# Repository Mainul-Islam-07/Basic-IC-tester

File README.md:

# Basic-IC-tester

TinkerCad Simulation Links

https://www.tinkercad.com/things/fH9ZXDevmyo-ic-tester

https://www.tinkercad.com/things/dbMPnGqOklm-ic-tester

Features: 

1) Checks all ports of a basic logic ic (AND , OR, NOT, NOR, NAND, XOR gates) and detects the specific ic and show whether all the ports are okay or whether the ic is damaged. There are 3 slots for placing ICs to check as all basic ic pin configurations are not the same.

2) The output ( either the ic name , or if damaged displays damaged) is shown in a LCD displau

3) The output is then transmitted as msg to a phone number via Sim800L module

** Both hardware and software simulations were done.

The repository contains the pcb files as well as the arduino code required.

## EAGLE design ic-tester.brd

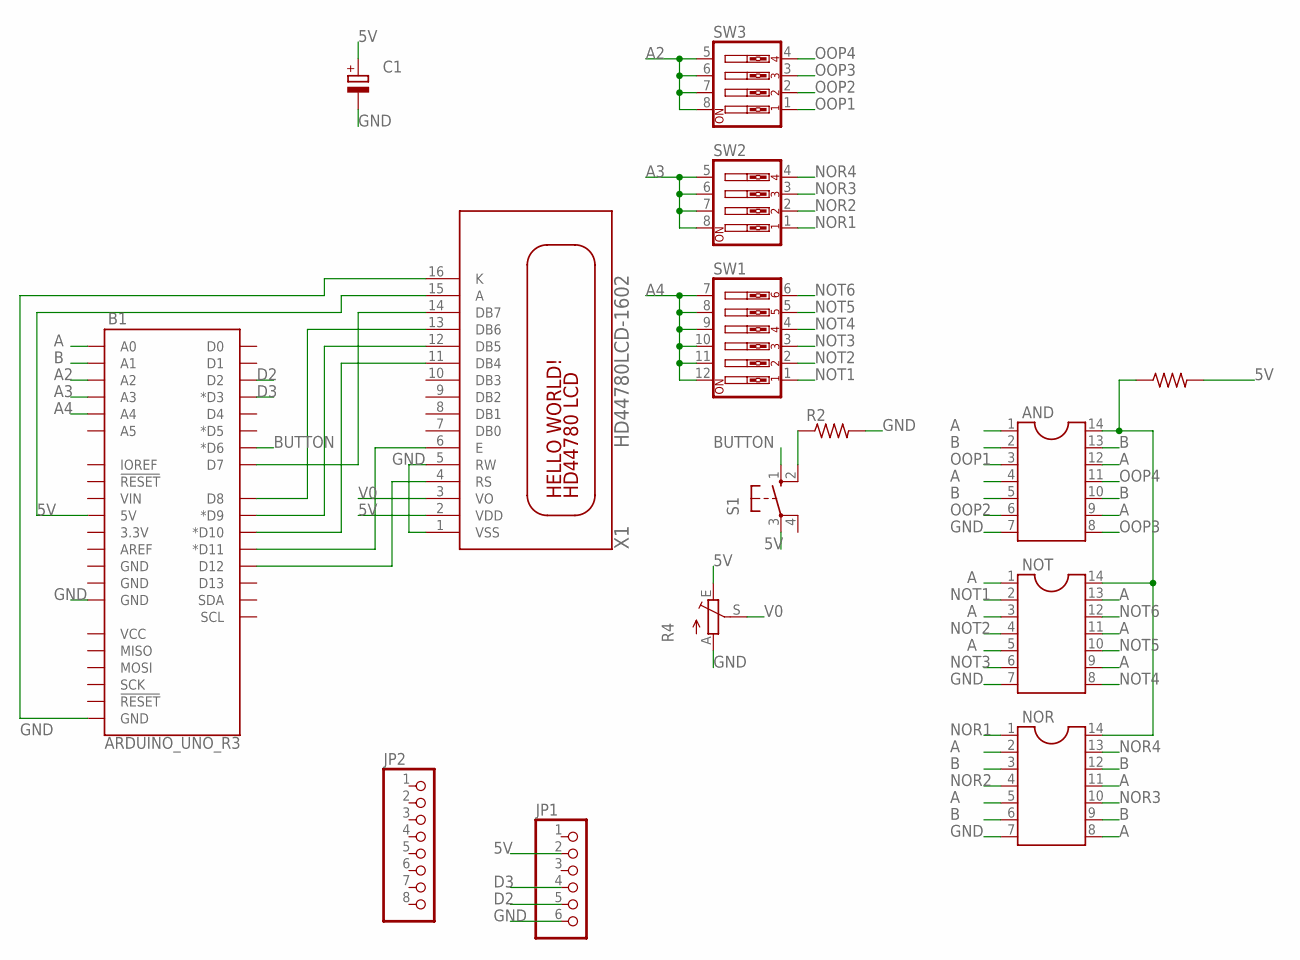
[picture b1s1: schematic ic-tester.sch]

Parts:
AND: DIL14
B1: ARDUINO_UNO_R3; ARDUINO_R3
C1: CPOL-EUE7.5-16; E7,5-16
JP1: PINHD-1X6; 1X06
JP2: PINHD-1X8BIG; 1X08-BIG
NOR: DIL14
NOT: DIL14
R1, R2: R-US_0204/7; 0204/7
R4: TRIM_EU-LI10; LI10
S1: 10-XX; B3F-10XX
SW1: SW_DIP-6; EDG-06
SW2, SW3: SW_DIP-4; EDG-04
X1: HD44780LCD-1602; LCD1602

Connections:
5V: B1.5V, C1.+, JP1.2, R1.2, R4.E, S1.3, X1.2 (VDD), X1.15 (A)
A: AND.1, AND.4, AND.9, AND.12, B1.A0, NOR.2, NOR.5, NOR.8, NOR.11, NOT.1, NOT.3, NOT.5, NOT.9, NOT.11, NOT.13
A2: B1.A2, SW3.5, SW3.6, SW3.7, SW3.8
A3: B1.A3, SW2.5, SW2.6, SW2.7, SW2.8
A4: B1.A4, SW1.7, SW1.8, SW1.9, SW1.10, SW1.11, SW1.12
B: AND.2, AND.5, AND.10, AND.13, B1.A1, NOR.3, NOR.6, NOR.9, NOR.12
BUTTON: B1.D6 (*D6), S1.1 (S)
D2: B1.D2, JP1.5
D3: B1.D3 (*D3), JP1.4
GND: AND.7, B1.GND@1 (GND), B1.GND@2 (GND), C1.-, JP1.6, NOR.7, NOT.7, R2.2, R4.A, X1.1 (VSS), X1.5 (RW), X1.16 (K)
unnamed: B1.D9 (*D9), X1.12 (DB5)
unnamed: B1.D7, X1.14 (DB7)
unnamed: R2.1, S1.2 (S1)
unnamed: B1.D8, X1.13 (DB6)
unnamed: B1.D10 (*D10), X1.11 (DB4)
unnamed: B1.D11 (*D11), X1.6 (E)
unnamed: B1.D12, X1.4 (RS)
unnamed: AND.14, NOR.14, NOT.14, R1.1
NOR1: NOR.1, SW2.1
NOR2: NOR.4, SW2.2
NOR3: NOR.10, SW2.3
NOR4: NOR.13, SW2.4
NOT1: NOT.2, SW1.1
NOT2: NOT.4, SW1.2
NOT3: NOT.6, SW1.3
NOT4: NOT.8, SW1.4
NOT5: NOT.10, SW1.5
NOT6: NOT.12, SW1.6
OOP1: AND.3, SW3.1
OOP2: AND.6, SW3.2
OOP3: AND.8, SW3.3
OOP4: AND.11, SW3.4
V0: R4.S, X1.3 (VO)

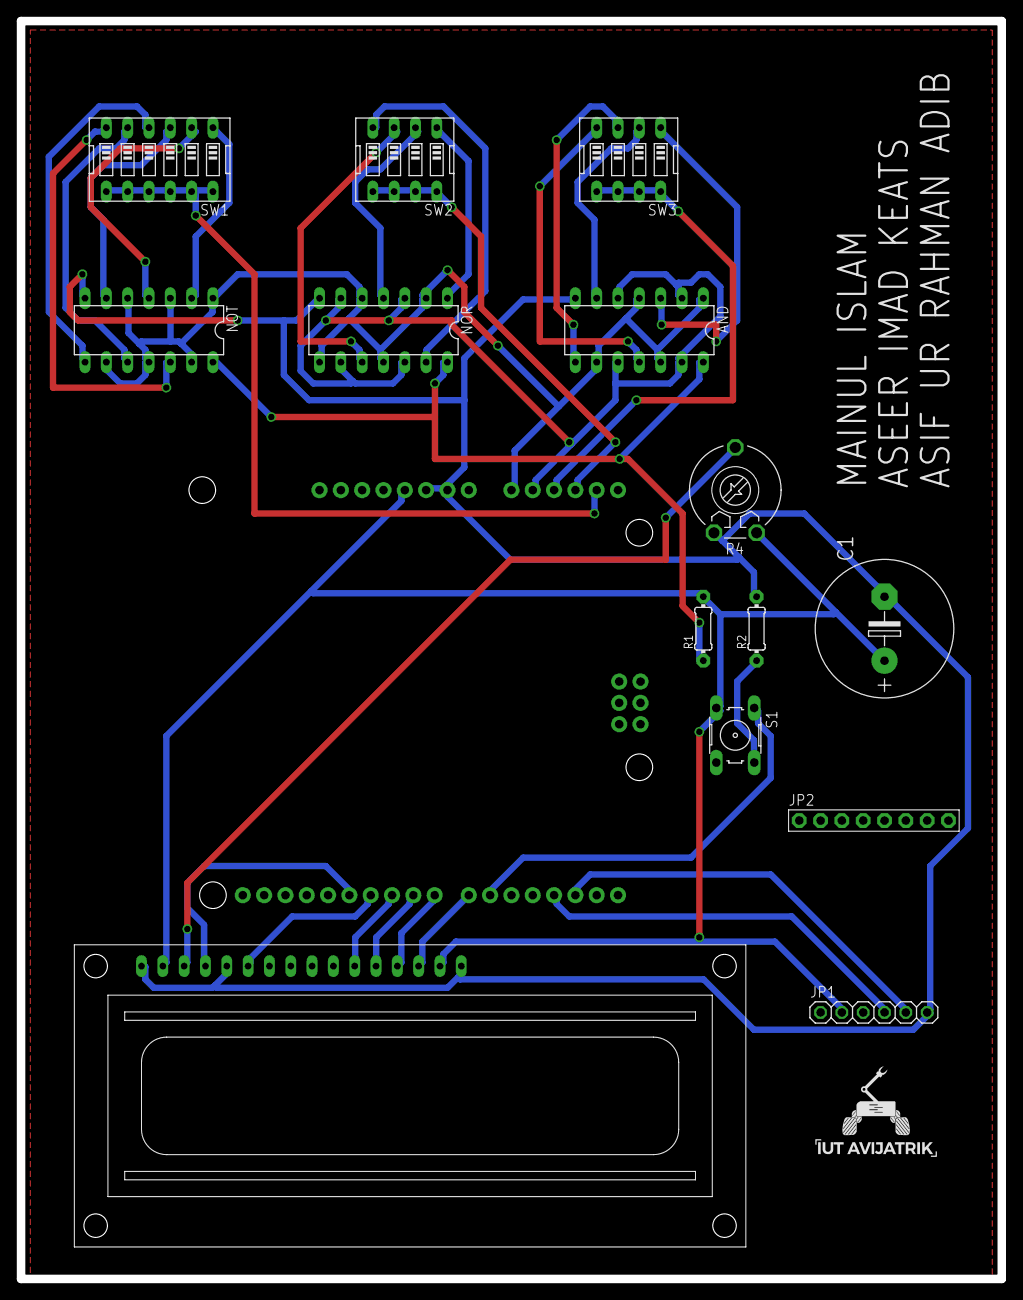
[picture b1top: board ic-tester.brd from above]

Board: 2 copper layers, 116.8 x 149.9 mm, 16 parts (1 on the bottom side), 33 nets.

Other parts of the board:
U$1: AVIJATRIK

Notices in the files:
parts and their libraries:
SparkFun-Boards: Licensing: Creative Commons ShareAlike 4.0 International - https://creativecommons.org/licenses/by-sa/4.0
